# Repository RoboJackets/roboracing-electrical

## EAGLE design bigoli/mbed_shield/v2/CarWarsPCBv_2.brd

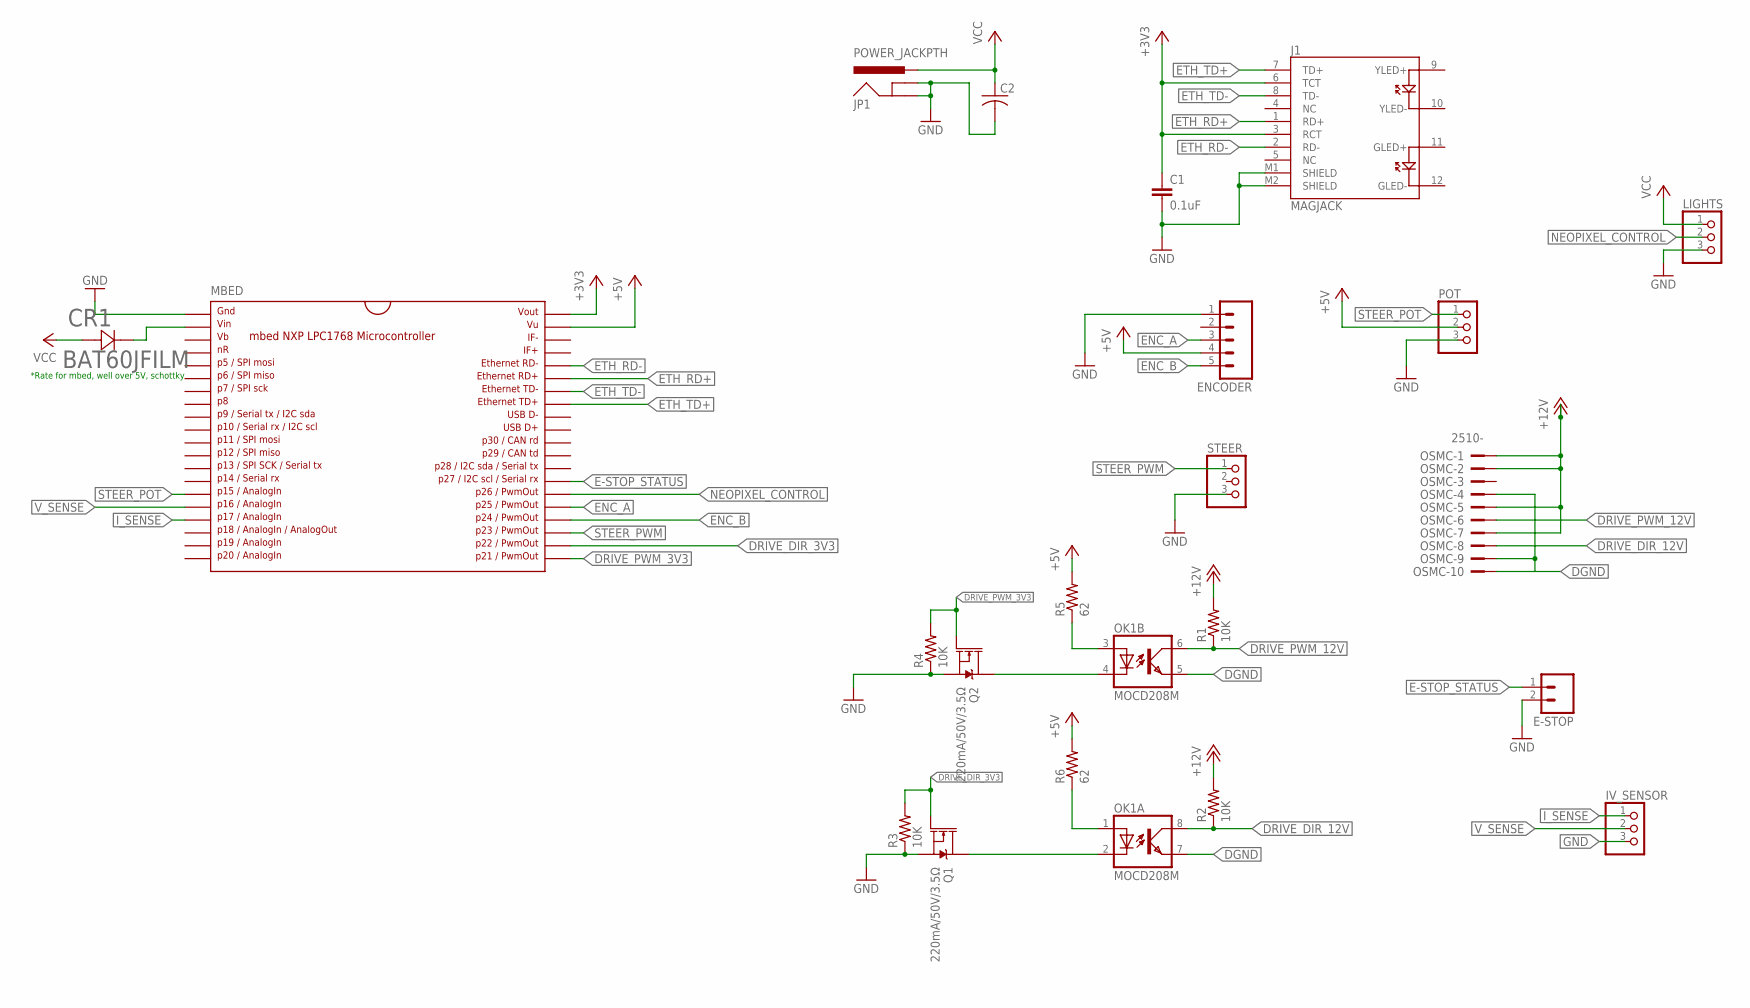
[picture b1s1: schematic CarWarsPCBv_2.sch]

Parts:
C1: 0.1uF; 0805
C2: C-USC0805; C0805
CR1: BAT60JFILM; SOD-323
E-STOP: M02PTH; 1X02
ENCODER: M05PTH; 1X05
IV_SENSOR: PINHD-1X3; 1X03
J1: MAGJACK
JP1: POWER_JACKPTH; POWER_JACK_PTH
LIGHTS: PINHD-1X3; 1X03
MBED: MBED1768; DIL40_0.9
OK1: MOCD208M; SOIC08-FAIRCHILD
OSMC: 2510-; PAK100/2500-10
POT: PINHD-1X3; 1X03
Q1, Q2: 220mA/50V/3.5Ω; SOT23-3
R1, R2, R3, R4: 10K; R0603
R5, R6: 62; R0603
STEER: PINHD-1X3; 1X03

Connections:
+3V3: C1.1, J1.3 (RCT), J1.6 (TCT), MBED.40
+5V: ENCODER.4, MBED.39, POT.2, R5.2, R6.2
+12V: OSMC.1, OSMC.2, OSMC.5, OSMC.7, R1.2, R2.2
DGND: OK1.5 (EMIT), OK1.7 (EMIT), OSMC.4, OSMC.9, OSMC.10
DRIVE_DIR_3V3: MBED.22, Q1.1 (G), R3.2
DRIVE_DIR_12V: OK1.8 (COL), OSMC.8, R2.1
DRIVE_PWM_3V3: MBED.21, Q2.1 (G), R4.2
DRIVE_PWM_12V: OK1.6 (COL), OSMC.6, R1.1
E-STOP_STATUS: E-STOP.1, MBED.27
ENC_A: ENCODER.3, MBED.25
ENC_B: ENCODER.5, MBED.24
ETH_RD+: J1.1 (RD+), MBED.35
ETH_RD-: J1.2 (RD-), MBED.36
ETH_TD+: J1.7 (TD+), MBED.33
ETH_TD-: J1.8 (TD-), MBED.34
GND: C1.2, C2.2, E-STOP.2, ENCODER.1, IV_SENSOR.3, J1.M1 (SHIELD), J1.M2 (SHIELD), JP1.GND, JP1.GNDBREAK, LIGHTS.3, MBED.1, POT.3, Q1.2 (S), Q2.2 (S), R3.1, R4.1, STEER.3
I_SENSE: IV_SENSOR.1, MBED.17
unnamed: CR1.1 (11), MBED.2
unnamed: OK1.2 (C), Q1.3 (D)
unnamed: OK1.4 (C), Q2.3 (D)
unnamed: OK1.3 (A), R5.1
unnamed: OK1.1 (A), R6.1
NEOPIXEL_CONTROL: LIGHTS.2, MBED.26
STEER_POT: MBED.15, POT.1
STEER_PWM: MBED.23, STEER.1
VCC: C2.1, CR1.2 (22), JP1.PWR, LIGHTS.1
V_SENSE: IV_SENSOR.2, MBED.16

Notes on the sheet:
*Rate for mbed, well over 5V, schottky

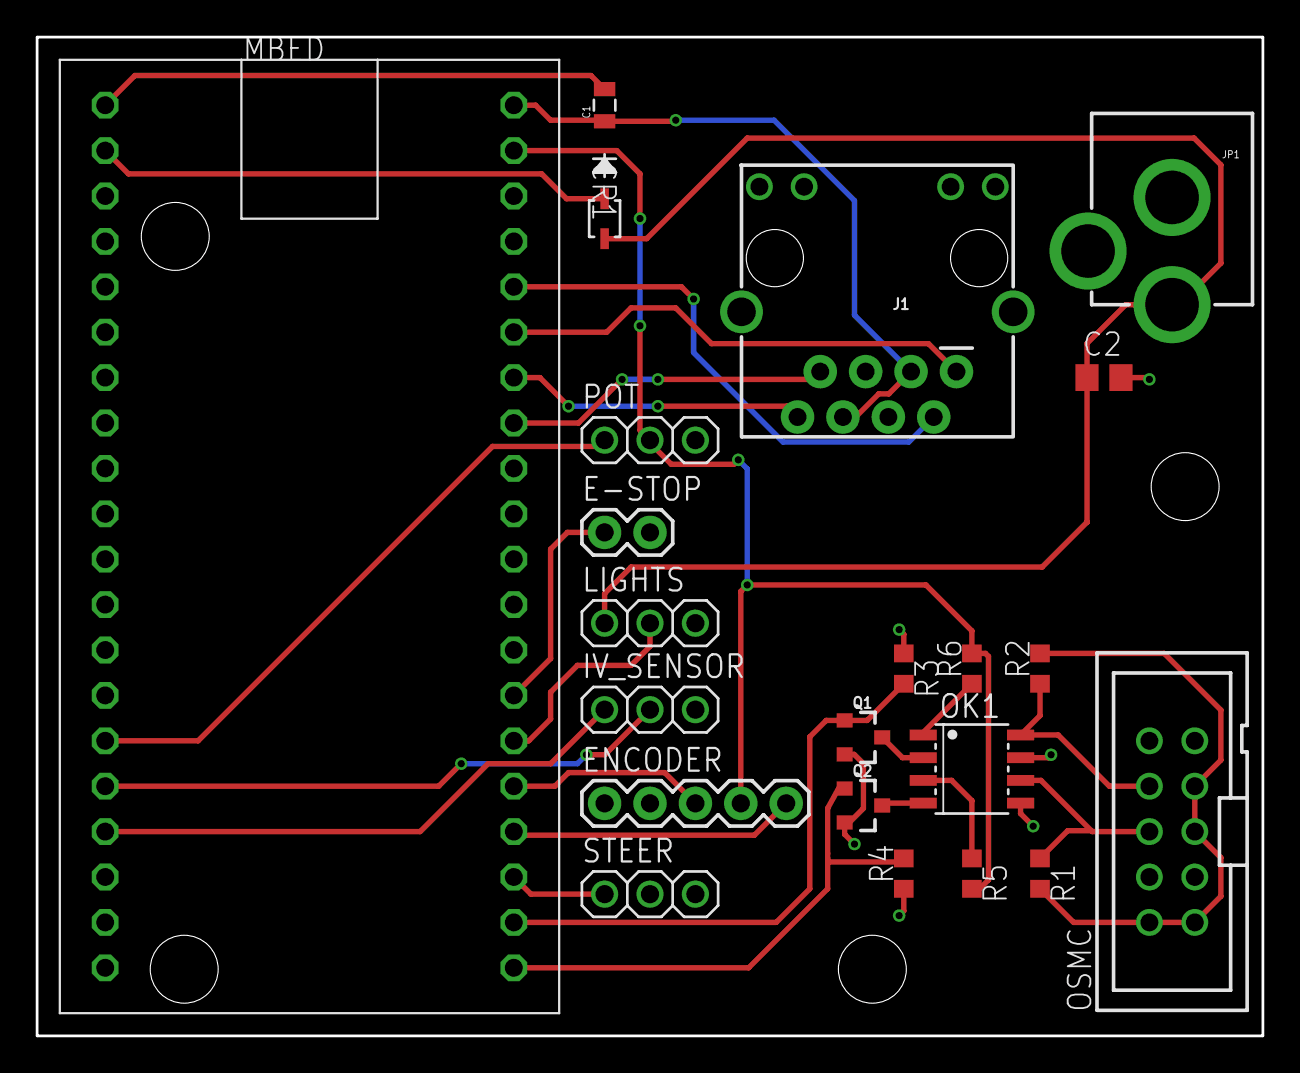
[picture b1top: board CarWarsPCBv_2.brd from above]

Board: 2 copper layers, 68.6 x 55.9 mm, 22 parts (0 on the bottom side), 27 nets.

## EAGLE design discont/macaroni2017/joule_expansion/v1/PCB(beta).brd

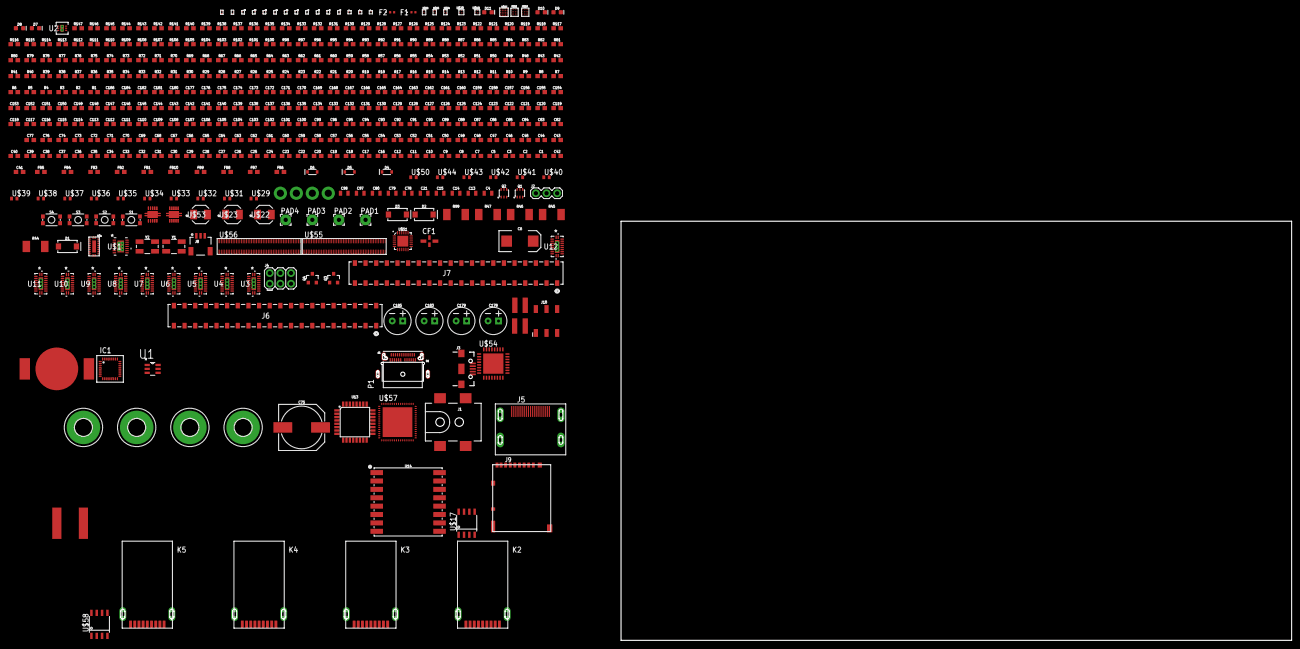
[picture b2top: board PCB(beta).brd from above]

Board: 2 copper layers, 464 parts (0 on the bottom side), 425 nets, no tracks yet.

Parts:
C1, C2, C3, C7, C12, C24, C25, C26, C27, C28, C29, C30, C31, C32, C33, C34, C35, C36, C37, C38, C39, C40, C43, C44, C45, C46, C47, C48, C49, C50, C51, C52, C53, C54, C55, C56, C57, C58, C59, C60, C61, C62, C63, C64, C65, C66, C67, C68, C69, C70, C71, C86, C87, C88, C90, C91, C100, C101, C102, C109, C110, C111, C112, C113, C114, C115, C116, C117, C118, C119, C120, C121, C122, C123, C124, C125, C126, C127, C132, C133, C137, C138, C140, C141, C142, C143, C144, C145, C146, C147, C148, C149, C150, C151, C152, C153, C154, C157, C158, C159, C160, C161, C162, C163, C164, C169, C170, C171, C172, C176, C177, C180, C181, C182, C184, C186: 0.1uF; 0603
C4, C13, C14, C15, C21, C78, C79, C80, C97, C98: 22uF; 0805
C5, C82: 47pF; 0603
C6: 100uF; EIA7343
C8, C9, C10, C17, C23, C72, C76, C89, C92, C93, C94, C99, C105, C106, C107, C108, C128, C129, C139, C155, C156: 10uF; 0603
C11, C18, C19, C20, C83, C103, C104, C136: 1.0uF; 0603
C16, C73, C74: 2.2uF; 0603
C22: 220PF; 0603
C41, C42: 0.22uF; 0603
C75: 100uF; NIC_10X10.5_CAP
C77: 100pF; 0603
C84, C85: 220pF; 0603
C95: 47nF; 0603
C96, C173, C175: 4.7uF; 0603
C130, C131: 22pF; 0603
C134, C135: 18pF; 0603
C165, C166, C167, C168: 1nF; 0603
C174: 10nF; 0603
C178, C179, C183, C185: 150uF; CPOL-RADIAL-2.5MM-6.5MM
CF1: NFM18PC104R1E3D; NFM21C
D1: 5A/20V/550mV; SMA-DIODE
D2, D3: 200mA/30V; SMA-DIODE
D4, D5, D6: 0.5A/40V/420mV; SOD-323
D7, D8, D9, D10: GREEN; LED-0603
D11: LED-0603
F1, F2: 043503.5KRHF; 0435SERIES
FB1, FB2, FB3, FB4, FB5: 120Ω/1.3A; 0603
FB6, FB7, FB8, FB9: 220@100MHz; 0603
FB10: 220@100Mhz; 0603
H1, H2, H3, H4: MOUNT-PAD-ROUND4.1; 4,1-PAD
IC1: FT232RQ; MLF32
J1: 5.5x2.1mm Barrel; POWER_JACK_SMD
J2: 1X03
J3: USB-B-MICRO-SMD
J4: FEMALE 2x3; 2X3
J5: 685119134923
J6, J7: SSM-120-S-DV; CON40_2X20_DU_SSM
J8: 1X03-1MM-RA
J9: DM3AT-SF-PEJM5
J10: 2X3_SMD
K2, K3, K4, K5: 692112030100
P1: 1-2295018-2; TE_1-2295018-2
PAD1, PAD2, PAD3, PAD4: 2,54/1,0
Q1, Q2: SC70-6
Q3, Q4: 220mA/50V/3.5Ω; SOT23-3
R1, R4, R5, R10, R18, R19, R21, R68, R69, R70, R71, R72, R73, R74, R75, R76, R80, R85, R86, R87, R88, R89, R91, R98, R108: 0; 0603
R2: 18.2k; 0603
R3, R12, R13, R14, R15, R17, R64, R65, R66, R67, R77, R93, R96, R100, R109, R110, R111, R112, R113, R114, R115, R119, R120, R121, R122, R123, R124, R125, R131, R143, R144, R146, R147: 10k; 0603
R6, R7, R11, R20, R25, R26, R27, R28, R31, R32, R33, R34, R35, R36, R37, R38, R48, R49, R50, R51, R52, R53, R58, R59, R60, R81, R82, R90, R94, R97, R101, R102, R103, R104, R106: 100k; 0603
R8: 36.5k; 0603
R9: 110k; 0603
R16, R24, R29, R30, R39, R54, R55, R56, R57, R83: 200k; 0603
R22, R23, R117, R118: 2.7k; 0603
R40, R41, R42, R43, R92, R95: 1.1k; 0603
R44, R45, R46, R47: 560; 2010
R61, R105: 100; 0603
R62, R63: 3.3k; 0603
R78, R84: 1k; 0603
R79: 1.5k; 0603
R99: 510; 2010
R107: 120k; 0603
R116: 4.99k; 0603
R126, R138, R139, R140, R141: 1M; 0603
R127, R128, R130, R132, R134, R135, R136, R137: 4.7k; 0603
R129: 9.53k; 0603
R133: 90.9k; 0603
R142, R145: 25.5k; 0603
S1, S2, S3, S4: TACTILE_SWITCH_SMD_4.6X2.8MM
U1: TPS2553DBVT; SOT95P280X145-6N
U2: TLV62084DSGR; DSG8_0P9X1P6
U3, U4, U5, U6, U7, U8, U9, U10, U11, U12: LSF0108RKSR; RKS20_1P1X3P1
U13: ATMEGA328P_TQFP; TQFP32-08
U14: 433MHz; RFM69HCW-XXXS2
U$1: TPS63021DSJR; DSJ14_2P85X1P58
U$2, U$3, U$5: LFTVS18-1F3_FLIPCHIP; 4-UFBGA
U$4: 20-TQFP
U$6, U$7, U$8, U$9, U$10, U$11: TCE0806S-350-2P-T200; 0302_(0806_METRIC)
U$12, U$13, U$14, U$15: TCE0806G-900-2P-T200; 0302_(0806_METRIC)
U$16: TSM-102-01-L-DV-TR; 4X-.145X.05_SQ
U$17: M24M02-DRMN6TP; SOIC8
U$18: FPF3042UCX; 16-WLCSP
U$19, U$20: FPF2495UCX; 9-WLCSP
U$21: FAN48623UC50X_SWITCHING_REGULATOR; 16-WLCSP
U$22, U$23, U$53: SPM4012T-1R0M; IND_SPM4020
U$24, U$25, U$26: ECMF02-2BF3; 5-WLCSP
U$27: IP4856CX25; 25-WLCSP
U$28, U$52: SSM3K56CTL3FCT-ND_NCHAN_MOSFET; 3-XFDFN
U$29, U$31, U$32, U$33, U$34, U$35, U$36, U$37, U$38, U$39, U$40, U$41, U$42, U$43, U$44, U$50: 0402
U$30: BK-916-TR_12MM_COINCELL; 12MM_COINCELL
U$45, U$46, U$47, U$48: 92320A282_1/8_SPACER; 1/8"RING
U$49: ASPIAIG-S8050
U$51: BQ25892RTWT; WQFN-24
U$54: PS8203TQFN32GTR-A3; TQFN32
U$55, U$56: DF40C-100DS-0.4V(51)_100PINCONNECTOR; 100-DF40
U$57: TUSB8041; QFN64-9X9
U$58: ADP1706ARDZ-1.1-R7; SOIC8
U$59, U$60: TPS2561DRCT; 10-VSON
Y1: 16MHz; CRYSTAL-SMD-5X3.2-4PAD
Y2: 24MHz; CRYSTAL-SMD-5X3.2-4PAD

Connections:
+1.8V: C18.1, C19.1, C21.1, C26.1, C44.1, C45.1, C47.1, C49.1, C51.1, C57.1, C59.1, C61.1, C63.1, C65.1, C66.1, C102.1, C104.1, FB5.1, J7.12, R7.2, R9.2, R25.2, R26.2, R33.2, R34.2, R35.2, R36.2, R48.2, R49.2, R50.2, R58.2, R92.2, R93.2, R117.2, R118.2, U2.5, U3.2, U4.2, U5.2, U6.2, U7.2, U8.2, U9.2, U10.2, U11.2, U12.2, U$23.1, U$37.1, U$54.30
+1V1: C148.1, C149.1, C150.1, C151.1, C152.1, C153.1, C154.1, C155.1, C175.1, U$57.5, U$57.8, U$57.13, U$57.21, U$57.28, U$57.31, U$57.51, U$57.57, U$58.5, U$58.6, U$58.7
+3V3: C13.1, C14.1, C15.1, C16.1, C50.1, C67.1, C68.1, C101.1, C103.1, C173.1, C186.1, FB4.1, FB6.2, J7.6, J7.8, Q3.1, Q4.1, R6.2, R12.2, R13.2, R14.2, R15.2, R16.2, R18.2, R24.2, R27.2, R28.2, R29.2, R30.2, R31.2, R32.2, R37.2, R38.2, R39.2, R51.2, R52.2, R53.2, R54.2, R55.2, R56.2, R57.2, R59.2, R96.2, R109.2, R110.2, R113.2, R114.2, R119.2, R122.2, R125.2, R134.2, R135.2, R136.2, R137.2, R143.2, R144.2, R146.2, R147.2, U7.19, U7.20, U14.13, U$1.3, U$1.4, U$1.5, U$38.1, U$54.11, U$58.1, U$58.3, U$58.4
+3V3_HUB: C156.1, C157.1, C158.1, C159.1, C160.1, FB6.1
+5V: C8.1, C39.1, C69.1, C70.1, C73.1, C74.1, C78.1, C79.1, C80.1, C90.1, C133.1, C176.1, C177.1, D3.A, D4.A, D5.A, D6.A, J7.2, J7.4, J8.1, J10.2, R3.2, R44.2, R45.2, R46.2, R47.2, R82.2, R121.2, R123.2, R124.2, U1.1, U13.4, U13.6, U13.18, U$19.A1, U$19.B1, U$20.A1, U$20.B1, U$21.B3, U$21.B4, U$39.1, U$59.2_1, U$59.2_2, U$59.3_1, U$59.3_2, U$60.2_1, U$60.2_2, U$60.3_1, U$60.3_2
+V1P8V_MICROSD: C87.1, FB5.2, U$27.B3
+V1P8V_SW: U2.7, U$23.2
+V3P3V_FT23RQ: C24.1, C25.1, IC1.1, IC1.16
+V3P3V_MICROSD: C88.1, C89.1, FB4.2, J9.4, U$27.A4, U$27.C4, U$34.1
+V3P3V_SW_L1: U$1.8, U$1.9, U$22.2
+V3P3V_SW_L2: U$1.6, U$1.7, U$22.1
+V3P3V_VINA: C12.1, U$1.1
+V5P0V_CONN: U$19.A3, U$19.B3
+V5P0V_D: C40.1, C41.1, C42.1, D6.C, J5.18
+V5P0V_SW: U$21.C3, U$21.C4, U$49.2
+V5P0V_USBA: C6.A, C7.1, U1.6
+V5P0V_VCONN: C119.1, U$55.P$41
+VBATTERY: C5.1, C123.1, PAD1.1, PAD2.1, U$50.1, U$55.P$92
+VBOOST: C95.2, U$51.21
+VBUS: C22.1, C23.1, C75.+, C120.1, CF1.1, U$18.A1, U$18.B1, U$18.C1, U$20.A3, U$20.B3, U$55.P$99
+VBUS_USBC: F2.2, P1.A4, P1.A9, P1.B4, P1.B9, U$5.A1, U$5.A2
+VBUS_USBC_F: CF1.3, F2.1
+VDC_IN: C3.1, C4.1, C72.1, C118.1, F1.2, U$18.C4, U$55.P$37
+VDC_IN_F: C2.1, D1.C, F1.1, U$2.A1, U$2.A2
+VDC_IN_F_D: D1.A, J1.VIN0
+VDD1: C55.1, C56.1, C71.1, C122.1, J6.34, R10.2, R60.2, R61.2, R64.2, R66.2, R69.2, U$35.1, U$55.P$36
+VDD3: C53.1, C54.1, C121.1, J6.40, R5.2, R81.2, U$36.1, U$55.P$30
+VDD_USBC_MUX: C28.1, C29.1, C30.1, R18.1, U$4.P$1, U$4.P$6, U$4.P$10
+VFTDI_VCC_5P0V: D2.C, D3.C, IC1.19
+VIN_CHRG: C91.1, C92.1, C93.1, U$18.A2, U$18.A3, U$18.B3, U$18.C3, U$51.1
+VLDO_SDCARD: C83.1, U$27.B4
+VREGN: C96.1, R99.2, R100.2, R101.2, R106.2, U$51.22
+VRTC: C117.1, R95.1, U$55.P$11
+VSYS: C9.1, C10.1, C11.1, C17.1, C20.1, C76.1, C77.1, C97.1, C98.1, C105.1, C106.1, C107.1, C108.1, C109.1, C110.1, C111.1, C112.1, C113.1, C114.1, C115.1, C116.1, R84.2, R86.2, R87.2, R97.2, R102.2, R103.2, U2.V, U2.V_1, U$1.10, U$1.11, U$21.A3, U$21.A4, U$49.1, U$51.15, U$51.16, U$53.1, U$55.P$2, U$55.P$5, U$55.P$7, U$55.P$12, U$55.P$15, U$55.P$17
+VTC_R: R95.2, U$29.1, U$30.P$1, U$30.P$2
+VUSB_IN: FB3.2, J3.VBUS, U$33.1
+VUSB_IN_FILT: C86.1, D2.A, FB3.1, R11.2
+VUSB_IN_FILT_R: J2.1, R11.1
+V_CHRG_LX: C95.1, U$51.19, U$51.20, U$53.2
AVS_M_CLK_A1: U10.3, U$56.P$52
AVS_M_CLK_A1_LS: J7.26, U10.18
AVS_M_CLK_B1: U10.8, U$56.P$62
AVS_M_CLK_B1_LS: J7.24, U10.13
AVS_M_DATA_1: U10.9, U$56.P$66
AVS_M_DATA_1_LS: J7.22, U10.12
BATT_GND: PAD3.1, PAD4.1, R1.2
BLDRW_0_PWM: U10.5, U$56.P$56
BLDRW_0_PWM_LS: J7.17, U10.16
BOOST_DCDC_BYP_N: R84.1, R85.2, U$21.C1
BTN_N: R60.1, S2.3, S2.4, U$41.1, U$55.P$84
CHRG_EN_N: R104.2, U$52.P$1, U$55.P$35
CHRG_EN_N_R: R103.1, U$51.9, U$52.P$3
CHRG_ILIM: R105.2, U$51.10
CHRG_INT_N: U$51.7, U$55.P$40
CHRG_LED_A: D11.A, R99.1
CHRG_OTG: R102.1, U$51.8
CHRG_PG_N: D11.C, R100.1, U$51.3
CHRG_PMID: C94.1, U$51.23
CHRG_PSEL: R97.1, R98.2, U$51.2
CHRG_QON: R108.1, U$51.12
CHRG_STAT: R101.1, U$51.4
CHRG_TS: R106.1, R107.2, U$51.11
CHS_GND: C1.2, C2.2, J3.SHIELD1, J3.SHIELD2, J3.SHIELD3, R71.2, R72.2, R73.2, R74.2, U$2.B1, U$2.B2, U$3.B1, U$3.B2, U$5.B1, U$5.B2, U$6.P5_1, U$6.P5_2, U$6.P6_1, U$6.P6_2, U$7.P5_1, U$7.P5_2, U$7.P6_1, U$7.P6_2, U$8.P5_1, U$8.P5_2, U$8.P6_1, U$8.P6_2, U$9.P5_1, U$9.P5_2, U$9.P6_1, U$9.P6_2, U$10.P5_1, U$10.P5_2, U$10.P6_1, U$10.P6_2, U$11.P5_1, U$11.P5_2, U$11.P6_1, U$11.P6_2, U$12.P5_1, U$12.P5_2, U$12.P6_1, U$12.P6_2, U$13.P5_1, U$13.P5_2, U$13.P6_1, U$13.P6_2, U$14.P5_1, U$14.P5_2, U$14.P6_1, U$14.P6_2, U$15.P5_1, U$15.P5_2, U$15.P6_1, U$15.P6_2, U$24.GND, U$25.GND, U$26.GND, U$31.2, U$32.2, U$33.2, U$34.2
CLK_19P2M: U7.6, U$55.P$71
CLK_19P2M_LS: J6.5, U7.15
CODEC_MCLK: U6.8, U$55.P$43
CODEC_MCLK_LS: J6.20, U6.13
DCIN_EN: R109.1, R111.2, U$54.8
DDI1_CTRL_CLK: R118.1, U$54.31, U$55.P$68
DDI1_CTRL_DAT: R117.1, U$54.32, U$55.P$70
DF_IN: R75.2, U$18.D3
DISPLAY_0_BIAS_EN: U10.4, U$56.P$64
DISPLAY_0_BIAS_EN_LS: J7.13, U10.17
DISPLAY_0_BKLT_EN: U10.6, U$56.P$58
DISPLAY_0_BKLT_EN_LS: J7.15, U10.15
DISPLAY_0_RST_N: U10.10, U$56.P$68
DISPLAY_0_RST_N_LS: J7.11, U10.11
DN1_VBUS: C178.1, C180.1, FB7.1, U$59.9_1, U$59.9_2
DN2_VBUS: C179.1, C181.1, FB8.1, U$59.8_1, U$59.8_2
DN3_VBUS: C182.1, C183.1, FB9.1, U$60.9_1, U$60.9_2
EEPROM_E2: R66.1, R67.2, U$17.3
EEPROM_VCC: R69.1, U$17.8
EEPROM_WC_N: R64.1, R65.2, U$17.7
EN6: C52.1, R39.1, U8.19, U8.20
EN_1P8V: R10.1, U2.1
EN_3P3V: R5.1, U$1.12
EN_5P0V: R81.1, R83.2, U$21.A1
EQ: R110.1, R112.2, U$54.13
FAN_CTRL: J8.2, R96.1
FB_1P8V: R8.2, R9.1, U2.4
FLASH_RST_N: U11.4, U$56.P$71
FLASH_RST_N_LS: J7.18, U11.17
FLASH_TORCH: U11.5, U$56.P$73
FLASH_TORCH_LS: J7.16, U11.16
FLASH_TRIGGER: U11.3, U$56.P$69
FLASH_TRIGGER_LS: J7.20, U11.18
FTDI_USB_DN: IC1.15, U$26.A1
FTDI_USB_DP: IC1.14, U$26.B1
FTDI_USB_FILT_DN: J3.D-, U$26.A2
FTDI_USB_FILT_DP: J3.D+, U$26.B2
FTDI_USB_ID: J3.ID, R17.2
GND: C1.1, C3.2, C4.2, C5.2, C6.C, C7.2, C8.2, C9.2, C10.2, C11.2, C12.2, C13.2, C14.2, C15.2, C16.2, C17.2, C18.2, C19.2, C20.2, C21.2, C22.2, C23.2, C24.2, C25.2, C26.2, C27.2, C28.2, C29.2, C30.2, C39.2, C40.2, C41.2, C42.2, C43.2, C44.2, C45.2, C46.2, C47.2, C48.2, C49.2, C50.2, C51.2, C52.2, C53.2, C54.2, C55.2, C56.2, C57.2, C58.2, C59.2, C60.2, C61.2, C62.2, C63.2, C64.2, C65.2, C66.2, C67.2, C68.2, C69.2, C70.2, C71.2, C72.2, C73.2, C74.2, C75.-, C76.2, C77.2, C78.2, C79.2, C80.2, C82.2, C83.2, C84.2, C85.2, C86.2, C87.2, C88.2, C89.2, C90.2, C91.2, C92.2, C93.2, C94.2, C96.2, C97.2, C98.2, C99.2, C100.2, C101.2, C102.2, C103.2, C104.2, C105.2, C106.2, C107.2, C108.2, C109.2, C110.2, C111.2, C112.2, C113.2, C114.2, C115.2, C116.2, C117.2, C118.2, C119.2, C120.2, C121.2, C122.2, C123.2, C124.2, C125.2, C126.2, C127.2, C128.2, C129.2, C130.1, C131.1, C132.2, C133.2, C134.1, C135.1, C136.2, C139.2, C148.2, C149.2, C150.2, C151.2, C152.2, C153.2, C154.2, C155.2, C156.2, C157.2, C158.2, C159.2, C160.2, C161.2, C162.2, C163.2, C164.2, C165.1, C165.2, C166.1, C166.2, C167.1, C167.2, C168.1, C168.2, C169.1, C169.2, C170.1, C170.2, C171.1, C171.2, C172.1, C172.2, C173.2, C174.2, C175.2, C176.2, C177.2, C178.2, C179.2, C180.2, C181.2, C182.2, C183.2, C184.2, C185.2, C186.2, CF1.2@1, H1.B4,1, H2.B4,1, H3.B4,1, H4.B4,1, IC1.4, IC1.17, IC1.20, IC1.24, IC1.26, J1.P$4, J2.3, J3.GND, J4.1, J5.2, J5.5, J5.8, J5.11, J6.36, J6.37, J6.38, J6.39, J7.1, J7.3, J7.5, J7.7, J7.9, J7.14, J8.3, J9.6, J9.B, J9.MOUNT0, J9.MOUNT1, J9.MOUNT2, J9.MOUNT3, J10.6, K2.4, K2.7, K3.4, K3.7, K4.4, K5.4, P1.A1, P1.A12, P1.B1, P1.B12, Q1.1, Q1.4, Q2.1, Q2.4, R1.1, R2.1, R8.1, R17.1, R19.1, R20.1, R62.1, R63.1, R65.1, R67.1, R71.1, R72.1, R73.1, R74.1, R75.1, R76.1, R77.1, R78.1, R79.1, R83.1, R85.1, R90.1, R94.1, R98.1, R104.1, R105.1, R107.1, R111.1, R112.1, R115.1, R116.1, R120.1, R127.1, R128.1, R129.1, R130.1, R131.1, R132.1, R138.1, R138.2, R139.1, R139.2, R140.1, R140.2, R141.1, R141.2, R142.1, R145.1, S1.1, S1.2, S2.1, S2.2, S4.1, S4.2, U1.2, U2.2, U2.3, U3.1, U3.21, U4.1, U4.21, U5.1, U5.21, U6.1, U6.21, U7.1, U7.21, U8.1, U8.21, U9.1, U9.21, U10.1, U10.21, U11.1, U11.21, U12.1, U12.21, U13.3, U13.5, U13.21, U14.1, U14.8, U14.10, U$1.2, U$1.13, U$1.15, U$3.A1, U$3.A2, U$4.P$5, U$4.P$11, U$4.P$20, U$4.P$21, U$17.4, U$18.D1, U$18.D2, U$19.A2, U$19.B2, U$20.A2, U$20.B2, U$21.B2, U$21.C2, U$21.D1, U$21.D2, U$21.D3, U$21.D4, U$27.C3, U$28.P$2, U$29.2, U$30.P$3, U$35.2, U$36.2, U$37.2, U$38.2, U$39.2, U$40.2, U$41.2, U$42.2, U$43.2, U$44.2, U$45.P$1, U$46.P$1, U$47.P$1, U$48.P$1, U$50.2, U$51.17, U$51.18, U$51.EP, U$52.P$2, U$54.14, U$54.EXP, U$55.P$10, U$55.P$19, U$55.P$48, U$55.P$54, U$55.P$60, U$55.P$66, U$55.P$72, U$55.P$75, U$55.P$82, U$55.P$86, U$55.P$96, U$55.P$98, U$55.P$100, U$56.P$2, U$56.P$5, U$56.P$8, U$56.P$10, U$56.P$16, U$56.P$17, U$56.P$23, U$56.P$24, U$56.P$29, U$56.P$30, U$56.P$35, U$56.P$36, U$56.P$41, U$56.P$42, U$56.P$48, U$56.P$54, U$56.P$60, U$56.P$61, U$56.P$67, U$56.P$74, U$56.P$80, U$56.P$84, U$56.P$85, U$56.P$90, U$56.P$91, U$56.P$93, U$56.P$96, U$56.P$99, U$57.16, U$57.34, U$57.52, U$57.63, U$57.EXP, U$58.2, U$59.1_1, U$59.1_2, U$59.PAD1, U$59.PAD2, U$59.PAD3, U$60.1_1, U$60.1_2, U$60.PAD1, U$60.PAD2, U$60.PAD3
GPIO_22: U7.3, U$55.P$94
GPIO_22_LS: J6.1, U7.18
GRST#: C136.1, U$57.50
HDMI_CEXT: C100.1, U$54.17
HDMI_CLK_CONN_DN: J5.12, U$13.P2_1, U$13.P2_2, U$13.P2_3
HDMI_CLK_CONN_DP: J5.10, U$13.P1_1, U$13.P1_2, U$13.P1_3
HDMI_CLK_C_DN: C32.2, U$54.10
HDMI_CLK_C_DP: C31.2, U$54.9
HDMI_CLK_DN: C32.1, U$55.P$46
HDMI_CLK_DP: C31.1, U$55.P$44
HDMI_DAT0_CONN_DN: J5.9, U$12.P2_1, U$12.P2_2, U$12.P2_3
HDMI_DAT0_CONN_DP: J5.7, U$12.P1_1, U$12.P1_2, U$12.P1_3
HDMI_DAT1_CONN_DN: J5.6, U$14.P2_1, U$14.P2_2, U$14.P2_3
HDMI_DAT1_CONN_DP: J5.4, U$14.P1_1, U$14.P1_2, U$14.P1_3
HDMI_DAT2_CONN_DN: J5.3, U$15.P2_1, U$15.P2_2, U$15.P2_3
HDMI_DAT2_CONN_DP: J5.1, U$15.P1_1, U$15.P1_2, U$15.P1_3
HDMI_OB_CLK_DN: U$13.P3_1, U$13.P3_2, U$13.P3_3, U$54.18
HDMI_OB_CLK_DP: U$13.P4_1, U$13.P4_2, U$13.P4_3, U$54.19
HDMI_OB_DAT0_DN: U$12.P3_1, U$12.P3_2, U$12.P3_3, U$54.21
HDMI_OB_DAT1_DN: U$14.P3_1, U$14.P3_2, U$14.P3_3, U$54.23
HDMI_OB_DAT1_DP: U$14.P4_1, U$14.P4_2, U$14.P4_3, U$54.24
HDMI_OB_DAT2_DN: U$15.P3_1, U$15.P3_2, U$15.P3_3, U$54.26
HDMI_OB_DAT2_DP: U$15.P4_1, U$15.P4_2, U$15.P4_3, U$54.27
HDMI_OB_SCL: J5.15, R22.2, U$54.28
HDMI_OB_SCL_D: D4.C, R22.1
HDMI_OB_SDA: J5.16, R23.2, U$54.29
HDMI_OB_SDA_D: D5.C, R23.1
HDMI_PRE: R119.1, R120.2, U$54.15
HDMI_REXT: R116.2, U$54.16
HDMI_TX_0_C_DN: C34.2, U$54.7
HDMI_TX_0_C_DP: C33.2, U$54.6
HDMI_TX_0_DN: C34.1, U$55.P$62
HDMI_TX_0_DP: C33.1, U$55.P$64
HDMI_TX_1_C_DN: C37.2, U$54.5
HDMI_TX_1_C_DP: C35.2, U$54.4
HDMI_TX_1_DN: C37.1, U$55.P$58
HDMI_TX_1_DP: C35.1, U$55.P$56
HDMI_TX_2_C_DN: C38.2, U$54.2
HDMI_TX_2_C_DP: C36.2, U$54.1
HDMI_TX_2_DN: C38.1, U$55.P$50
HDMI_TX_2_DP: C36.1, U$55.P$52
HPD_SRC: R92.1, U$28.P$3, U$55.P$65
HPD_SRC_N: R93.1, R94.2, U$28.P$1, U$54.3
I2C_0_SCL: R34.1, R70.1, U7.8, U$51.5, U$55.P$57
I2C_0_SCL_EE_R: R70.2, U$17.6
I2C_0_SCL_LS: J6.13, R31.1, U7.13
I2C_0_SDA: R33.1, R68.2, U7.4, U$51.6, U$55.P$95
I2C_0_SDA_EE_R: R68.1, U$17.5
I2C_0_SDA_LS: J6.11, R32.1, U7.17
I2C_1_SCL: R48.1, U9.10, U$56.P$43
I2C_1_SDA: R58.1, U12.3, U$56.P$45
I2C_1_SDA_LS: J7.31, R59.1, U12.18
I2C_2_SCL: R49.1, U9.8, U$56.P$28
I2C_2_SCL_LS: J7.37, R51.1, U9.13
I2C_2_SDA: R50.1, U9.9, U$56.P$26
I2C_2_SDA_LS: J7.35, R52.1, R53.1, U9.11, U9.12
I2S_1_CLK: U6.9, U$55.P$39
I2S_1_CLK_LS: J6.18, U6.12
I2S_1_FS: U6.7, U$55.P$45
I2S_1_FS_LS: J6.16, U6.14
I2S_1_RXD: U6.6, U$55.P$47
I2S_1_RXD_LS: J6.12, U6.15
I2S_1_TXD: U6.5, U$55.P$49
I2S_1_TXD_LS: J6.14, U6.16
ILIM1: R142.2, U$59.7_1, U$59.7_2
ILIM2: R145.2, U$60.7_1, U$60.7_2
ISH_GPIO0_COL: D7.A, R44.1
ISH_GPIO0_COL_D: D7.C, Q1.3
ISH_GPIO1_COL: D8.A, R45.1
ISH_GPIO1_COL_D: D8.C, Q1.6
ISH_GPIO2_COL: D9.A, R46.1
ISH_GPIO2_COL_D: D9.C, Q2.3
ISH_GPIO3_COL: D10.A, R47.1
ISH_GPIO3_COL_D: D10.C, Q2.6
ISH_GPIO_0: R40.1, U8.6, U$55.P$25
ISH_GPIO_0_LS: J6.35, U8.15
ISH_GPIO_0_R: Q1.5, R40.2
ISH_GPIO_1: R41.1, U8.5, U$55.P$27
ISH_GPIO_1_LS: J6.33, U8.16
ISH_GPIO_1_R: Q1.2, R41.2
ISH_GPIO_2: R42.1, U4.8, U$55.P$32
ISH_GPIO_2_LS: J6.31, U4.13
ISH_GPIO_2_R: Q2.5, R42.2
ISH_GPIO_3: R43.1, U4.7, U$55.P$34
ISH_GPIO_3_LS: J6.29, U4.14
ISH_GPIO_3_R: Q2.2, R43.2
ISH_GPIO_4: U8.4, U$55.P$29
ISH_GPIO_4_LS: J6.27, U8.17
ISH_GPIO_5: U4.6, U$55.P$38
ISH_GPIO_5_LS: J6.25, U4.15
ISH_GPIO_6: U8.3, U$55.P$31
ISH_GPIO_6_LS: J6.23, U8.18
ISH_I2C_0_SCL: R25.1, U5.6, U$55.P$16
ISH_I2C_0_SCL_LS: J6.17, R27.1, U5.15
ISH_I2C_0_SDA: R26.1, U5.5, U$55.P$18
ISH_I2C_0_SDA_LS: J6.15, R28.1, U5.16
ISH_I2C_1_SCL: R36.1, U8.8, U$55.P$21
ISH_I2C_1_SCL_LS: J6.21, R37.1, U8.13
ISH_I2C_1_SDA: R35.1, U8.7, U$55.P$23
ISH_I2C_1_SDA_LS: J6.19, R38.1, U8.14
ISH_UART_0_CTS: U9.4, U$56.P$9
ISH_UART_0_CTS_LS: J7.40, U9.17
ISH_UART_0_RTS: U9.5, U$56.P$11
ISH_UART_0_RTS_LS: J7.38, U9.16
ISH_UART_0_RXD: U9.6, U$56.P$13
ISH_UART_0_RXD_LS: J7.36, U9.15
ISH_UART_0_TXD: U9.7, U$56.P$15
ISH_UART_0_TXD_LS: J7.34, U9.14
LS_CFG: R114.1, R115.2, U$54.20
LS_PD_N: R113.1, U$54.12
MICRO_RST: J10.5, R121.1, S4.3, S4.4, U13.29
unnamed: J10.4, U13.15
unnamed: J10.1, U13.16
unnamed: R2.2, U1.5
unnamed: J10.3, U13.17
unnamed: C130.2, U13.7, Y1.3
unnamed: C62.1, R56.1, U11.19, U11.20
unnamed: C131.2, U13.8, Y1.1
unnamed: Q3.3, R123.1, U13.30
unnamed: C48.1, R30.1, U6.19, U6.20
unnamed: C46.1, R29.1, U5.19, U5.20
unnamed: C43.1, R24.1, U4.19, U4.20
unnamed: C60.1, R55.1, U10.19, U10.20
unnamed: C132.1, U13.20
unnamed: C27.1, R16.1, U3.19, U3.20
unnamed: C64.1, R57.1, U12.19, U12.20
unnamed: R127.2, U$57.49
unnamed: C58.1, R54.1, U9.19, U9.20
unnamed: R129.2, U$57.64
unnamed: Q4.3, R124.1, U13.31
unnamed: R132.2, U$57.45
unnamed: R128.2, U$57.42
unnamed: R130.2, U$57.40
unnamed: R131.2, R133.2, U$57.48
unnamed: C140.1, U$57.27
unnamed: C141.1, U$57.26
unnamed: C142.1, U$57.20
unnamed: C143.1, U$57.19
unnamed: C144.1, U$57.12
unnamed: C145.1, U$57.11
unnamed: C147.1, U$57.4
unnamed: C146.1, U$57.3
unnamed: C161.1, FB7.2, K2.1
unnamed: C174.1, U$58.8
unnamed: C162.1, FB8.2
unnamed: C163.1, FB9.2, K4.1
unnamed: C184.1, C185.1, U$60.8_1, U$60.8_2
unnamed: C164.1, FB10.2, K5.1
OTG_EN: R80.1, U$55.P$69
OTG_EN_R: R80.2, U$20.C3
OTG_I_ADJ: R78.2, U$20.C2
OVERCUR1Z: R143.1, U$57.46, U$59.10_1, U$59.10_2
OVERCUR2Z: R144.1, U$57.47, U$59.6_1, U$59.6_2
OVERCUR3Z: R146.1, U$57.44, U$60.10_1, U$60.10_2
OVERCUR4Z: R147.1, U$57.43, U$60.6_1, U$60.6_2
PMIC_PWRBTN_N: R108.2, S1.3, S1.4, U$42.1, U$55.P$9
PMIC_PWRGOOD: U6.10, U$55.P$33
PMIC_PWRGOOD_LS: J6.9, U6.11
PMIC_RESET_N: U4.3, U$55.P$13
PMIC_RESET_N_LS: J6.3, U4.18
PMIC_SLPCLK_1: U9.3, U$56.P$7
PWM_0: U4.5, U$55.P$1
PWM_0_LS: J6.26, U4.16
PWM_1: U4.4, U$55.P$3
PWM_1_LS: J6.28, U4.17
PWM_2: U5.4, U$55.P$22
PWM_2_LS: J6.30, U5.17
PWM_3: U5.3, U$55.P$24
PWM_3_LS: J6.32, U5.18
PWRCTL1_BATEN1: R134.1, U$57.36, U$59.4_1, U$59.4_2
PWRCTL2_BATEN2: R135.1, U$57.35, U$59.5_1, U$59.5_2
PWRCTL3_BATEN3: R136.1, U$57.33, U$60.4_1, U$60.4_2
PWRCTL4_BATEN4: R137.1, U$57.32, U$60.5_1, U$60.5_2
PWRGOOD_1P8V: R7.1, U2.6
PWRGOOD_3P3V: R6.1, U$1.14
PWRGOOD_5P0V: R82.1, U$21.A2
RST_FT232RQ_N: IC1.18, J2.2
SDCARD_CD_N: R89.1, U$55.P$79
SDCARD_CD_N_CONN: J9.A, R89.2, U$27.D3
SDCARD_CLK: U$27.C1, U$55.P$73
SDCARD_CLK_CONN: C82.1, J9.5, R91.2
SDCARD_CLK_CONN_R: R91.1, U$27.C5
SDCARD_CMD: U$27.D2, U$55.P$89
SDCARD_CMD_CONN: J9.3, U$27.D4
SDCARD_D0: U$27.D1, U$55.P$81
SDCARD_D0_CONN: J9.7, U$27.D5
SDCARD_D1: U$27.E1, U$55.P$83
SDCARD_D1_CONN: J9.8, U$27.E5
SDCARD_D2: U$27.A1, U$55.P$85
SDCARD_D2_CONN: J9.1, U$27.A5
SDCARD_D3: U$27.B1, U$55.P$87
SDCARD_D3_CONN: J9.2, U$27.B5
SDCARD_LVL_CLK_FB: U$27.E2, U$55.P$67, U$55.P$77
SDCARD_LVL_CMD_DIR: U$27.A2, U$55.P$90
SDCARD_LVL_DAT_DIR: U$27.A3, U$27.E3
SDCARD_LVL_SEL: U$27.B2, U$55.P$88
SDCARD_PWR_DOWN_N: R88.1, R90.2, U$55.P$91
SDCARD_PWR_DOWN_N_R: R88.2, U$27.C2
SPI_0_CLK: U12.10, U$56.P$59
SPI_0_CLK_LS: J7.25, U12.11
SPI_0_FS0: U11.6, U$56.P$75
SPI_0_FS0_LS: J7.19, U11.15
SPI_0_FS1: U10.7, U$56.P$77
SPI_0_FS1_LS: J7.21, U10.14
SPI_0_FS2: U12.7, U$56.P$53
SPI_0_FS2_LS: J7.23, U12.14
SPI_0_MISO: U12.5, U$56.P$49
SPI_0_MISO_LS: J7.29, U12.16
SPI_0_MOSI: U12.9, U$56.P$57
SPI_0_MOSI_LS: J7.27, U12.12
SPI_1_CLK: U6.3, U$55.P$53
SPI_1_CLK_LS: J6.10, U6.18
SPI_1_FS0: U7.10, U$55.P$55
SPI_1_FS0_LS: J6.6, U7.11
SPI_1_FS2: U5.7, U$16.P$3, U$44.1, U$55.P$14
SPI_1_FS2_LS: J6.8, U5.14
SPI_1_FS2_PD: R62.2, U$16.P$4
SPI_1_MISO: U7.7, U$55.P$63
SPI_1_MISO_LS: J6.2, U7.14
SPI_1_MOSI: U6.4, U$55.P$51
SPI_1_MOSI_LS: J6.4, U6.17
UART_0_CTS: U12.4, U$56.P$47
UART_0_CTS_LS: J7.32, U12.17
UART_0_RTS: U12.8, U$56.P$55
UART_0_RTS_LS: J7.30, U12.13
UART_0_RXD: U12.6, U$56.P$51
UART_0_RXD_LS: J7.28, Q4.2, R125.1, U12.15
UART_0_TXD: U7.5, U$55.P$93
UART_0_TXD_LS: J6.7, Q3.2, R122.1, U7.16
UART_1_RXD: U4.10, U$55.P$26
UART_1_RXD_LS: J6.24, U4.11
UART_1_TXD: U4.9, U$16.P$1, U$43.1, U$55.P$28
UART_1_TXD_LS: J6.22, U4.12
UART_1_TXD_PD: R63.2, U$16.P$2
UART_2_CTS: U3.4, U$55.P$74
UART_2_CTS_LS: IC1.32, J4.6, R13.1, U3.17
UART_2_RTS: U3.3, U$55.P$76
UART_2_RTS_LS: IC1.8, J4.2, R12.1, U3.18
UART_2_RXD: U3.5, U$55.P$80
UART_2_RXD_LS: IC1.30, J4.4, R14.1, U3.16
UART_2_TXD: S3.1, S3.2, U3.6, U$40.1, U$55.P$78
UART_2_TXD_LS: IC1.2, J4.5, R15.1, U3.15
UART_2_TXD_PU: R61.1, S3.3, S3.4
USB2_0_DN: U$24.B1, U$55.P$8
USB2_0_DP: U$24.A1, U$55.P$6
USB2_1_DN: U$25.A2, U$56.P$63
USB2_1_DP: U$25.B2, U$56.P$65
USB3_0_MUX1_RX_DN: U$4.P$16, U$7.P3_1, U$7.P3_2, U$7.P3_3
USB3_0_MUX1_RX_DP: U$4.P$17, U$7.P4_1, U$7.P4_2, U$7.P4_3
USB3_0_MUX1_TX_DN: U$4.P$18, U$6.P3_1, U$6.P3_2, U$6.P3_3
USB3_0_MUX1_TX_DP: U$4.P$19, U$6.P4_1, U$6.P4_2, U$6.P4_3
USB3_0_MUX2_RX_DN: U$4.P$12, U$10.P3_1, U$10.P3_2, U$10.P3_3
USB3_0_MUX2_RX_DP: U$4.P$13, U$10.P4_1, U$10.P4_2, U$10.P4_3
USB3_0_MUX2_TX_DN: U$4.P$14, U$8.P3_1, U$8.P3_2, U$8.P3_3
USB3_0_MUX2_TX_DP: U$4.P$15, U$8.P4_1, U$8.P4_2, U$8.P4_3
USB3_0_RX_DN: U$4.P$8, U$56.P$44
USB3_0_RX_DP: U$4.P$7, U$56.P$46
USB3_0_TX_DN: U$4.P$4, U$56.P$6
USB3_0_TX_DP: U$4.P$3, U$56.P$4
USB3_1_RX_DN: U$9.P4_1, U$9.P4_2, U$9.P4_3, U$56.P$97
USB3_1_RX_DP: U$9.P3_1, U$9.P3_2, U$9.P3_3, U$56.P$95
USB3_1_TX_DN: U$11.P4_1, U$11.P4_2, U$11.P4_3, U$56.P$89
USB3_1_TX_DP: U$11.P3_1, U$11.P3_2, U$11.P3_3, U$56.P$87
USB3_CONN_EN: R4.1, U1.3
USB3_CONN_FLT: R3.1, R4.2, U1.4
USBA_USB2_1_DN: U$25.A1, U$57.54
USBA_USB2_1_DP: U$25.B1, U$57.53
USBA_USB3_1_RX_DN: U$9.P1_1, U$9.P1_2, U$9.P1_3, U$57.59
USBA_USB3_1_RX_DP: U$9.P2_1, U$9.P2_2, U$9.P2_3, U$57.58
USBA_USB3_1_TX_DN: C138.1, U$11.P1_1, U$11.P1_2, U$11.P1_3
USBA_USB3_1_TX_DP: C137.1, U$11.P2_1, U$11.P2_2, U$11.P2_3
USBC_PD: R19.2, U$4.P$2
USBC_SEL: R21.1, U$56.P$18
USBC_SEL_R: R20.2, R21.2, U$4.P$9
USBC_USB2_0_DN: P1.A7, P1.B7, U$24.B2
USBC_USB2_0_DP: P1.A6, P1.B6, U$24.A2
USBC_USB3_0_MUX1_RX_DN: P1.B10, U$7.P2_1, U$7.P2_2, U$7.P2_3
USBC_USB3_0_MUX1_RX_DP: P1.B11, U$7.P1_1, U$7.P1_2, U$7.P1_3
USBC_USB3_0_MUX1_TX_DN: P1.A3, U$6.P2_1, U$6.P2_2, U$6.P2_3
USBC_USB3_0_MUX1_TX_DP: P1.A2, U$6.P1_1, U$6.P1_2, U$6.P1_3
USBC_USB3_0_MUX2_RX_DN: P1.A10, U$10.P2_1, U$10.P2_2, U$10.P2_3
USBC_USB3_0_MUX2_RX_DP: P1.A11, U$10.P1_1, U$10.P1_2, U$10.P1_3
USBC_USB3_0_MUX2_TX_DN: P1.B3, U$8.P2_1, U$8.P2_2, U$8.P2_3
USBC_USB3_0_MUX2_TX_DP: P1.B2, U$8.P1_1, U$8.P1_2, U$8.P1_3
USB_DM_DN1: K2.2, U$57.2
USB_DM_DN2: K3.2, U$57.10
USB_DM_DN3: K4.2, U$57.18
USB_DM_DN4: K5.2, U$57.25
USB_DP_DN1: K2.3, U$57.1
USB_DP_DN2: K3.3, U$57.9
USB_DP_DN3: K4.3, U$57.17
USB_DP_DN4: K5.3, U$57.24
USB_SSRXM_DN1: K2.5, U$57.7
USB_SSRXM_DN2: K3.5, U$57.15
USB_SSRXM_DN3: K4.5, U$57.23
USB_SSRXM_DN4: K5.5, U$57.30
USB_SSRXP_DN1: K2.6, U$57.6
USB_SSRXP_DN2: K3.6, U$57.14
USB_SSRXP_DN3: K4.6, U$57.22
USB_SSRXP_DN4: K5.6, U$57.29
USB_SSTXM_DN1: C147.2, K2.8
USB_SSTXM_DN2: C144.2, K3.8
USB_SSTXM_DN3: C142.2, K4.8
USB_SSTXM_DN4: C140.2, K5.8
USB_SSTXP_DN1: C146.2, K2.9
USB_SSTXP_DN2: C145.2, K3.9
USB_SSTXP_DN3: C143.2, K4.9
USB_SSTXP_DN4: C141.2, K5.9
USB_TYPC_CC1: C85.1, FB2.2, U$55.P$59
USB_TYPC_CC2: C84.1, FB1.2, U$55.P$61
USB_TYPC_CONN_CC1: FB2.1, P1.A5, U$32.1
USB_TYPC_CONN_CC2: FB1.1, P1.B5, U$31.1
V+: C99.1, C124.1, C125.1, C126.1, C127.1, C128.1, C129.1, U$51.13, U$51.14, U$56.P$1, U$56.P$3, U$56.P$20, U$56.P$22, U$56.P$32, U$56.P$34
VBUS_HUB: C139.1, R133.1
VCONN_DCDC_EN: U$19.C3, U$55.P$97
VCONN_I_ADJ: R79.2, U$19.C2
VIN_EN: R77.2, U$18.C2
VIN_SEL: R76.2, U$18.D4
VSEL_5P0V: R86.1, R87.1, U$21.B1
X: C137.2, U$57.55
XI: C135.2, R126.2, U$57.62, Y2.3
XO: C134.2, R126.1, U$57.61, Y2.1
Y: C138.2, U$57.56

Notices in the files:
parts and their libraries:
SparkFun-Capacitors: Licensing: Creative Commons ShareAlike 4.0 International - https://creativecommons.org/licenses/by-sa/4.0
Wurth_Elektronik_Electromechanic_Input-O: Copyright: Würth Elektronik
